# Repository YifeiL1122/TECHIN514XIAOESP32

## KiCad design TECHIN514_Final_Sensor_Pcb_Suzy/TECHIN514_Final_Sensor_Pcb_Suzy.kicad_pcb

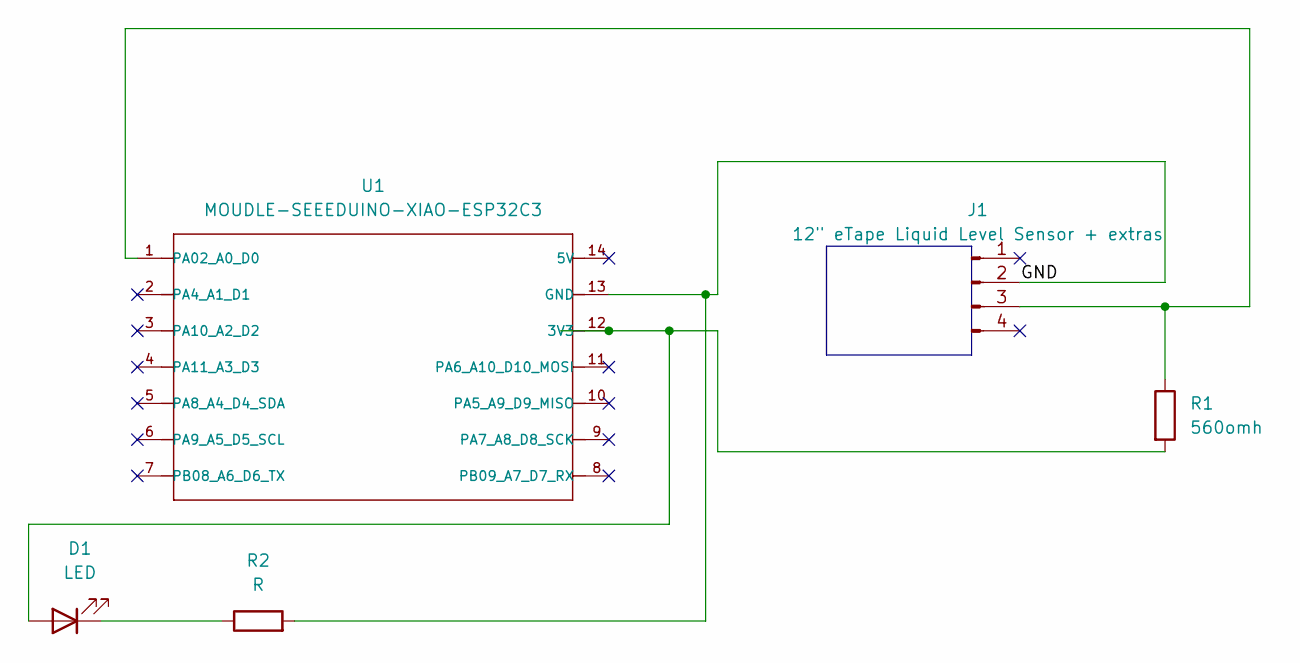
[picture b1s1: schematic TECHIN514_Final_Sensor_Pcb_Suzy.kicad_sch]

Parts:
D1: LED; LED_0805_2012Metric_Pad1.15x1.40mm_HandSolder
J1: 12" eTape Liquid Level Sensor + extras; PinHeader_1x04_P2.54mm_Vertical
R1: 560omh; R_0805_2012Metric_Pad1.20x1.40mm_HandSolder
R2: R; R_0805_2012Metric_Pad1.20x1.40mm_HandSolder
U1: MOUDLE-SEEEDUINO-XIAO-ESP32C3; MOUDLE14P-SMD-2.54-21X17.8MM

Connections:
/GND: J1.2, R2.2, U1.13 (GND)
unnamed: D1.2 (A), R1.2, U1.12 (3V3)
unnamed: D1.1 (K), R2.1
unnamed: J1.3, R1.1, U1.1 (PA02_A0_D0)

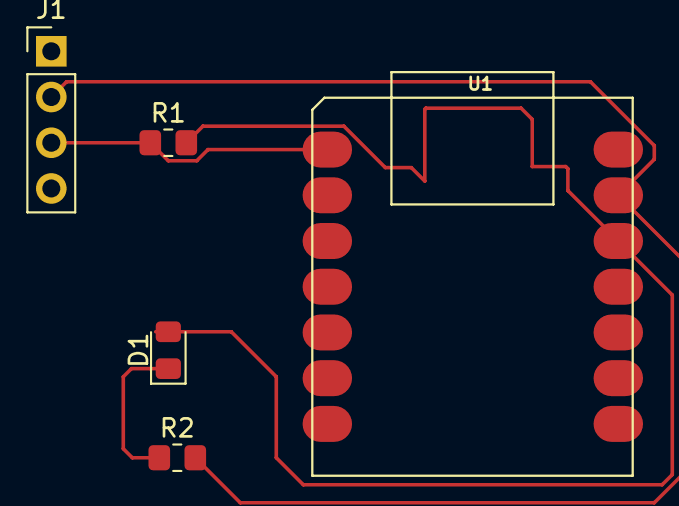
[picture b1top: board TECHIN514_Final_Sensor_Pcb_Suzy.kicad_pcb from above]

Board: 2 copper layers, 5 parts (0 on the bottom side), 4 nets.
